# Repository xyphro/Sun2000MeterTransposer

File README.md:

# Sun2000MeterTransposer

-> Enable other Smartmeters like SDM630 to connect to Huawei Sun2000 and look like DTSU-666.

This was my solution to address the fact, that DTSU-666 and its variants availability was "null".

It works rock solid since several months without a single interruption.

The project is based on RP2040 Raspberry pi Zero module. It will work on the Wifi variant too, but there is no network access enabled.

Note: I did not document the HW very well (yet), but want to share it still with the community. Build it at your own risk. The pinning of the 2 UART channels can be seen in s2kserver.py module (or schematic).

Warning: This project works with high voltage AC supply. You risk killing yourself, your family and friends, your pets. Take care and only work with line voltages when you are experienced in how much pain it causes to touch 230V :-)

# Folder structure

- hw: contains schematic / PCB in Eagle format.
- src: Micropython sourcecode - can be directly uploaded to RP2040 module using e.g. Thony IDE
- DinRainHousing: STL files for the 3D printed Dinrail housing
- photos: Some pictures of the actual build as inspiration

# Adjustments to other meters

Copy file sdm630.py and rename it to your meter name. Adjust it, such that the equivalent registers of your meter are read out and written to s2k module registers.
Within file s2kserver.py:
- You might need to change the UART settings like baudrate, parity in s2kserver during instatiation of uModBusSerial module.
- change ```from sdm630 import *``` to your module name

# Sourcecode orientation

main.py purpose is only to start s2kserver.py.
s2kserver instantiates 2 threads to server requests from Sun2000 inverter and poll SDM630 meter continously.

# Credits

Credits go to:
- uModbus [1] project. I changed the file slightly and included all dependencies within the src folder. Main modifications were done for speed/latency purposes
- DTSU666-Modbus [2] project: This project was of major support for the idea and to get register details. 
- GitHub user salakrzy
- Kai for testing it in endless debug sessions remotely whilr I was still busy ibstalling my solar installation and could not test myself
- Radek for making and providing his Chint DTSU666 module

# Compatibility

Tested with sun2000 3 phase 10kW inverters and proven working with spc147 and 148 firmware versions. As of now there is no newer one available.

# Updates

## 21st December 2022: 

Github user Radek made a module to support CHINT DTSU666 electricity meter (dtsu666.py). Thanks a lot for sharing it!

To make use of it adjust the settings within the user configurable settings in the file s2kserver.py.

Note that Chint DTSU666 usually uses those UART settings unless you configured it manually differently:

```
METER_UART_BAUDRATE = 9600
METER_UART_BITS     = 8
METER_UART_PARITY   = None
METER_UART_STOPBITS = 2
```

[1] https://github.com/pycom/pycom-modbus/tree/master/uModbus

[2] https://github.com/elfabriceu/DTSU666-Modbus

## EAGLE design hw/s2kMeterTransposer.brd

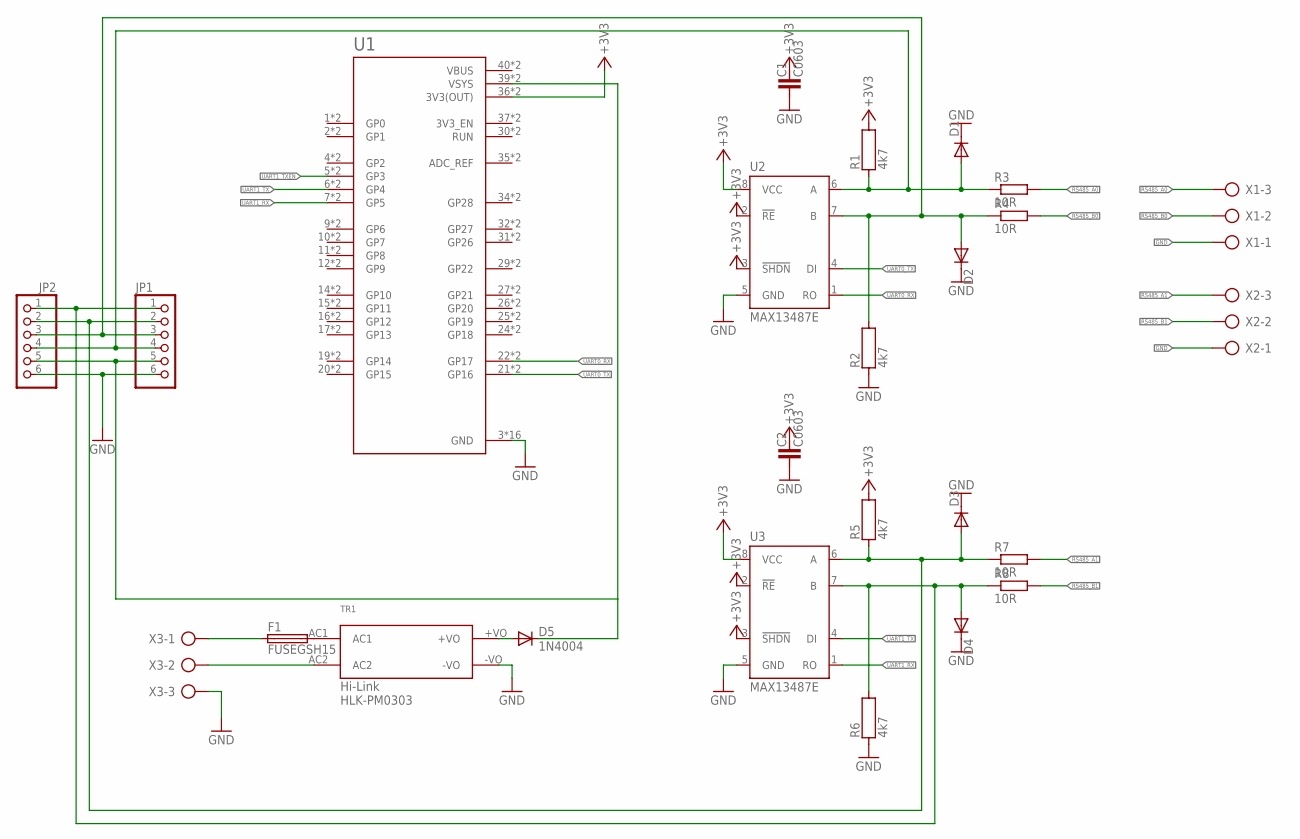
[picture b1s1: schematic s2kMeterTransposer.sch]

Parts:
C1, C2: C0603
D1, D2, D3, D4: DIODE-DO-214AC; DO-214AC
D5: 1N4004; DO41-10
F1: FUSEGSH15; GSH15
JP1: PINHD-1X6; 1X06
JP2: PINHD-1X6/90; 1X06/90
R1, R2, R5, R6: 4k7; R0603
R3, R4, R7, R8: 10R; R2010
TR1: HYX2018013001158
U1: RASPBERRY_PICO-NO_DEBUG; PICO-PKG-NO_DEBUG
U2, U3: MAX13487E; SO08
X1, X2, X3: AK500/3

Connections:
+3V3: C1.2, C2.2, R1.2, R5.2, U1.36 (3V3(OUT)), U1.P$36 (3V3(OUT)), U2.2 (!RE), U2.3 (!SHDN), U2.8 (VCC), U3.2 (!RE), U3.3 (!SHDN), U3.8 (VCC)
GND: C1.1, C2.1, D1.C, D2.C, D3.C, D4.C, JP1.6, JP2.6, R2.1, R6.1, TR1.-VO, U1.3 (GND), U1.8 (GND), U1.13 (GND), U1.18 (GND), U1.23 (GND), U1.28 (GND), U1.33 (GND), U1.38 (GND), U1.P$3 (GND), U1.P$8 (GND), U1.P$13 (GND), U1.P$18 (GND), U1.P$23 (GND), U1.P$28 (GND), U1.P$33 (GND), U1.P$38 (GND), U2.5 (GND), U3.5 (GND), X1.1, X2.1, X3.3
unnamed: D2.A, JP1.3, JP2.3, R2.2, R4.1, U2.7 (B)
unnamed: D1.A, JP1.4, JP2.4, R1.1, R3.1, U2.6 (A)
unnamed: D4.A, JP1.1, JP2.1, R6.2, R8.1, U3.7 (B)
unnamed: D3.A, JP1.2, JP2.2, R5.1, R7.1, U3.6 (A)
unnamed: F1.2, TR1.AC1
unnamed: F1.1, X3.1
unnamed: TR1.AC2, X3.2
unnamed: D5.A, TR1.+VO
unnamed: D5.C, JP1.5, JP2.5, U1.39 (VSYS), U1.P$39 (VSYS)
RS485_A0: R3.2, X1.3
RS485_A1: R7.2, X2.3
RS485_B0: R4.2, X1.2
RS485_B1: R8.2, X2.2
UART0_RX: U1.22 (GP17), U1.P$22 (GP17), U2.1 (RO)
UART0_TX: U1.21 (GP16), U1.P$21 (GP16), U2.4 (DI)
UART1_RX: U1.7 (GP5), U1.P$7 (GP5), U3.1 (RO)
UART1_TX: U1.6 (GP4), U1.P$6 (GP4), U3.4 (DI)
UART1_TXEN: U1.5 (GP3), U1.P$5 (GP3)
VBUS: U1.40 (VBUS), U1.P$40 (VBUS)

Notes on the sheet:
Hi-Link HLK-PM0303

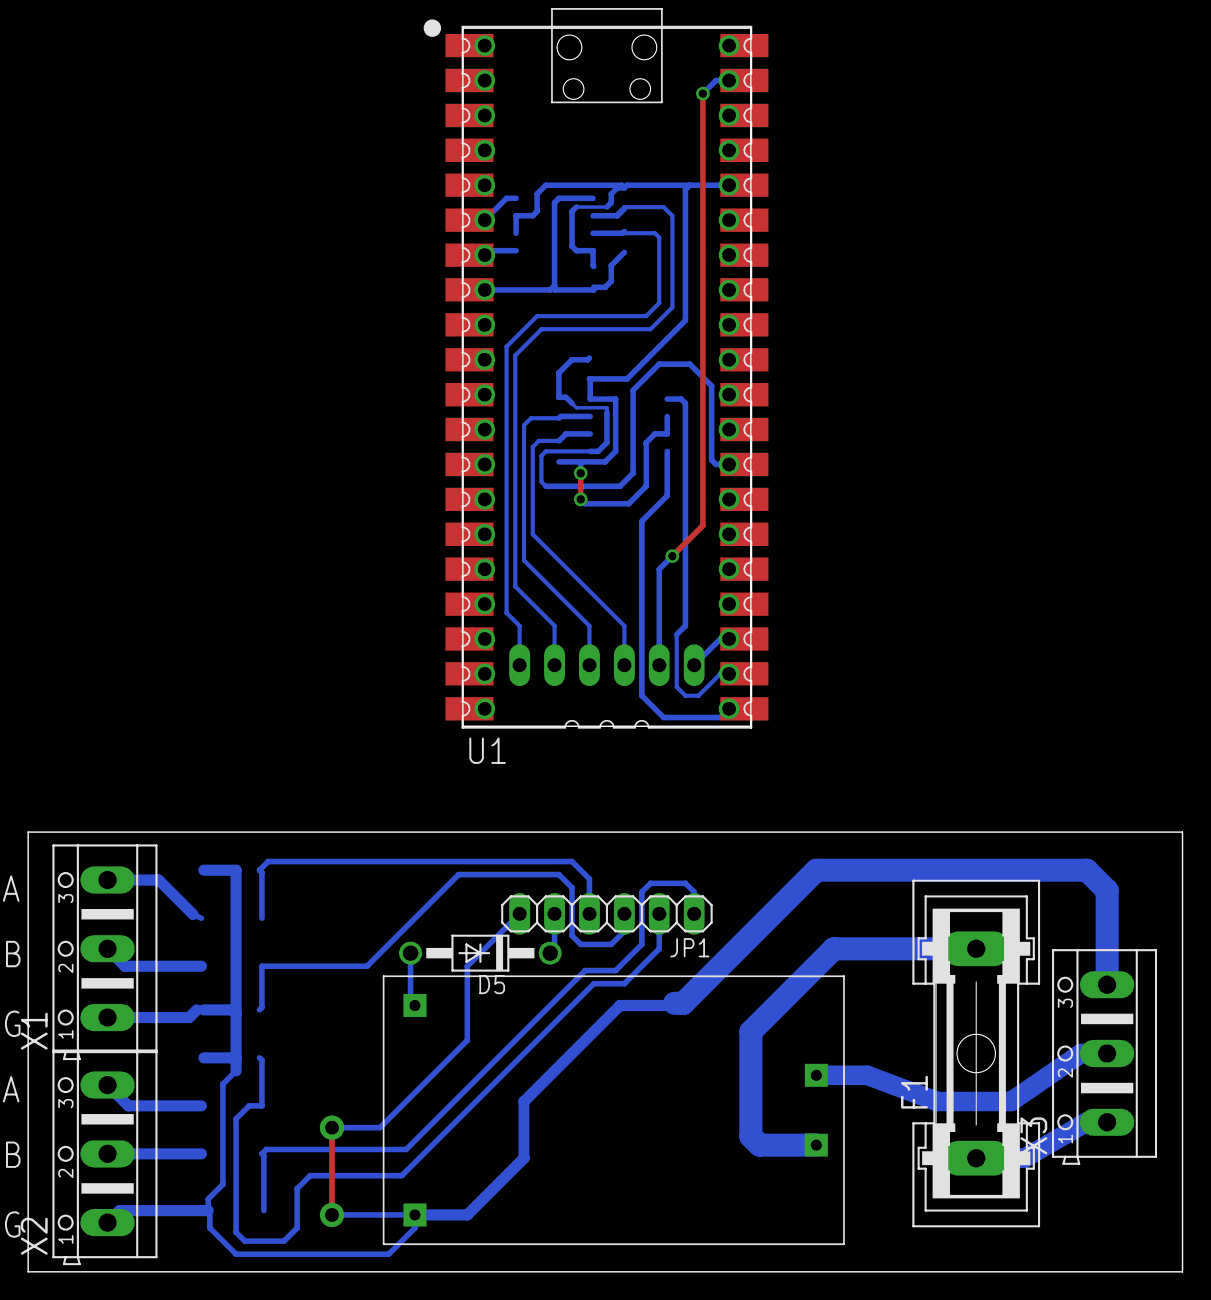
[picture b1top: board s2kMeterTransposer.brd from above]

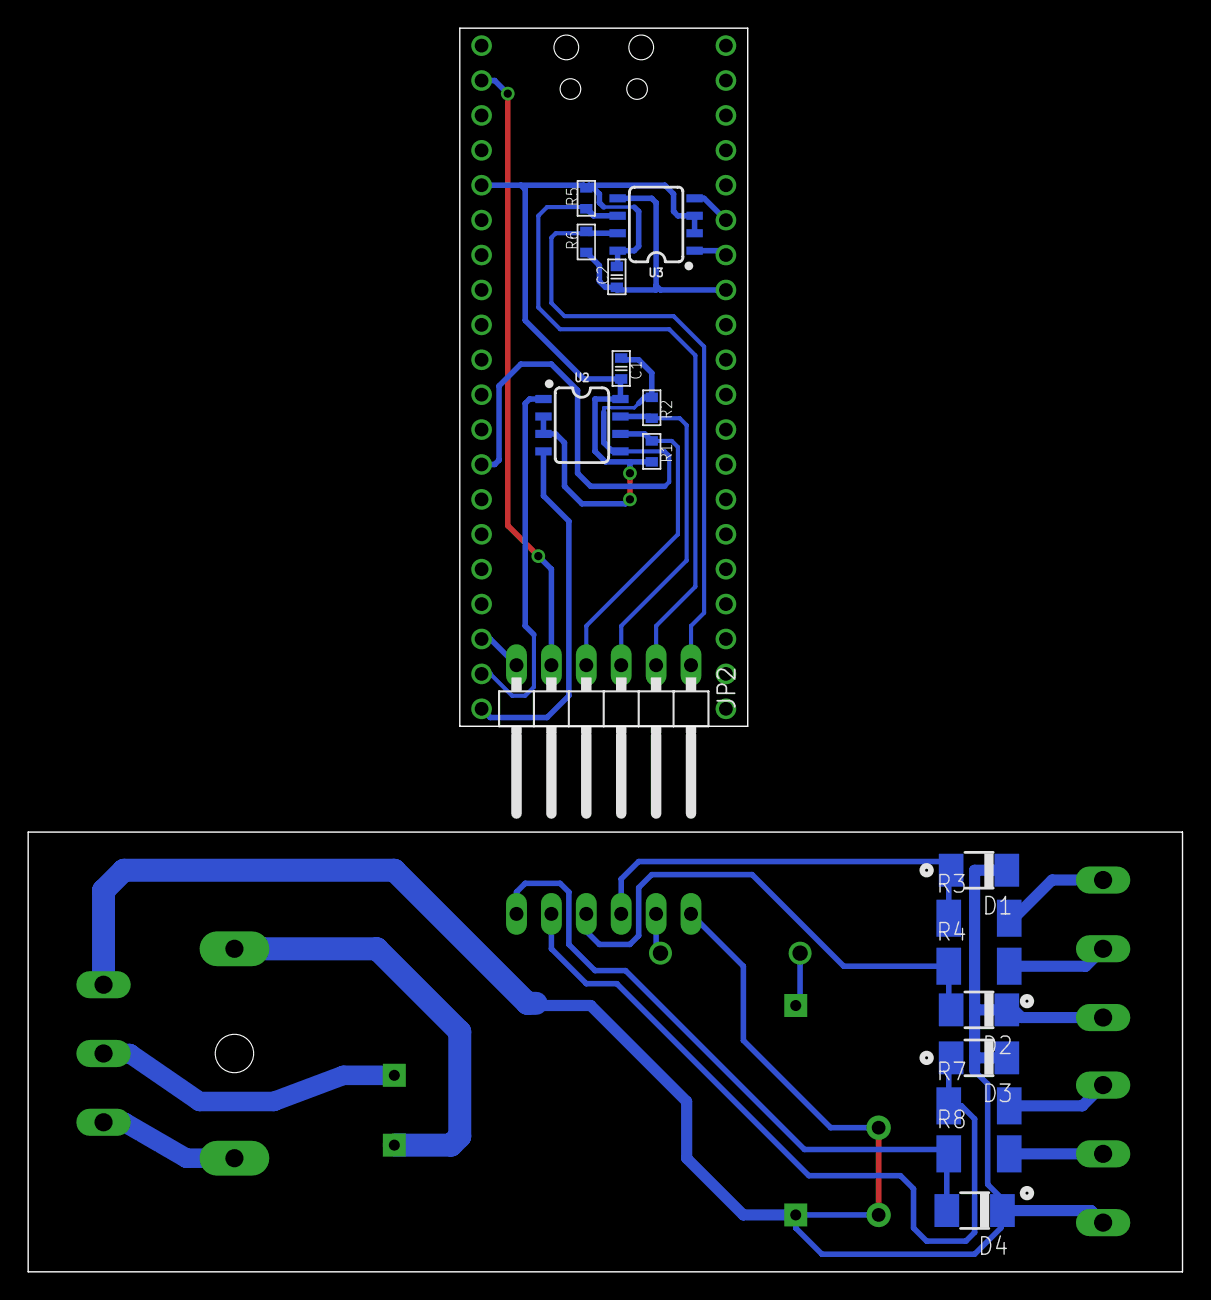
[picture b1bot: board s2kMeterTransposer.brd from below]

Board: 2 copper layers, 84.0 x 90.5 mm, 25 parts (17 on the bottom side), 21 nets.

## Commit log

2022-12-07 Add STL files for 3D printed housing
2022-12-07 Add Eagle layout and schematic
2022-12-15 Update README.md
    Add compatibility statement
2022-12-15 Update README.md
    Fix typo
2022-12-21 Added support for chint dtsu666 electricity meter and exposed user adjustable settings a bit better.
    Thanks a lot Radek for making this DTSU666 module!
2022-12-21 fix formating issues
2022-12-21 fix AGAIN formating issues :-/
